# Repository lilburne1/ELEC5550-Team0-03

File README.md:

This project reflects the hardware and software contributions of Team 0-03 for ELEC5550 in pursuit of a free space optical laser communication system.

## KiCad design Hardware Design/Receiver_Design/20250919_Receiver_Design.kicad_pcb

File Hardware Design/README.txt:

This folder includes the hardware design for ELEC5550 Team0-03's FSO communication system.
This includes:
    The KiCad schematic and PCB manufacturing files for the laser receiver circuit
    The KiCad schematic and PCB manufacturing files for the laser driver circuit
    The KiCad schematic and PCB manufacturing files for the mainboards
    The 3D printing and CAD files for the system's enclosure and laser lens holder

All these materials are covered under the CERN-OHL-P license, as attached

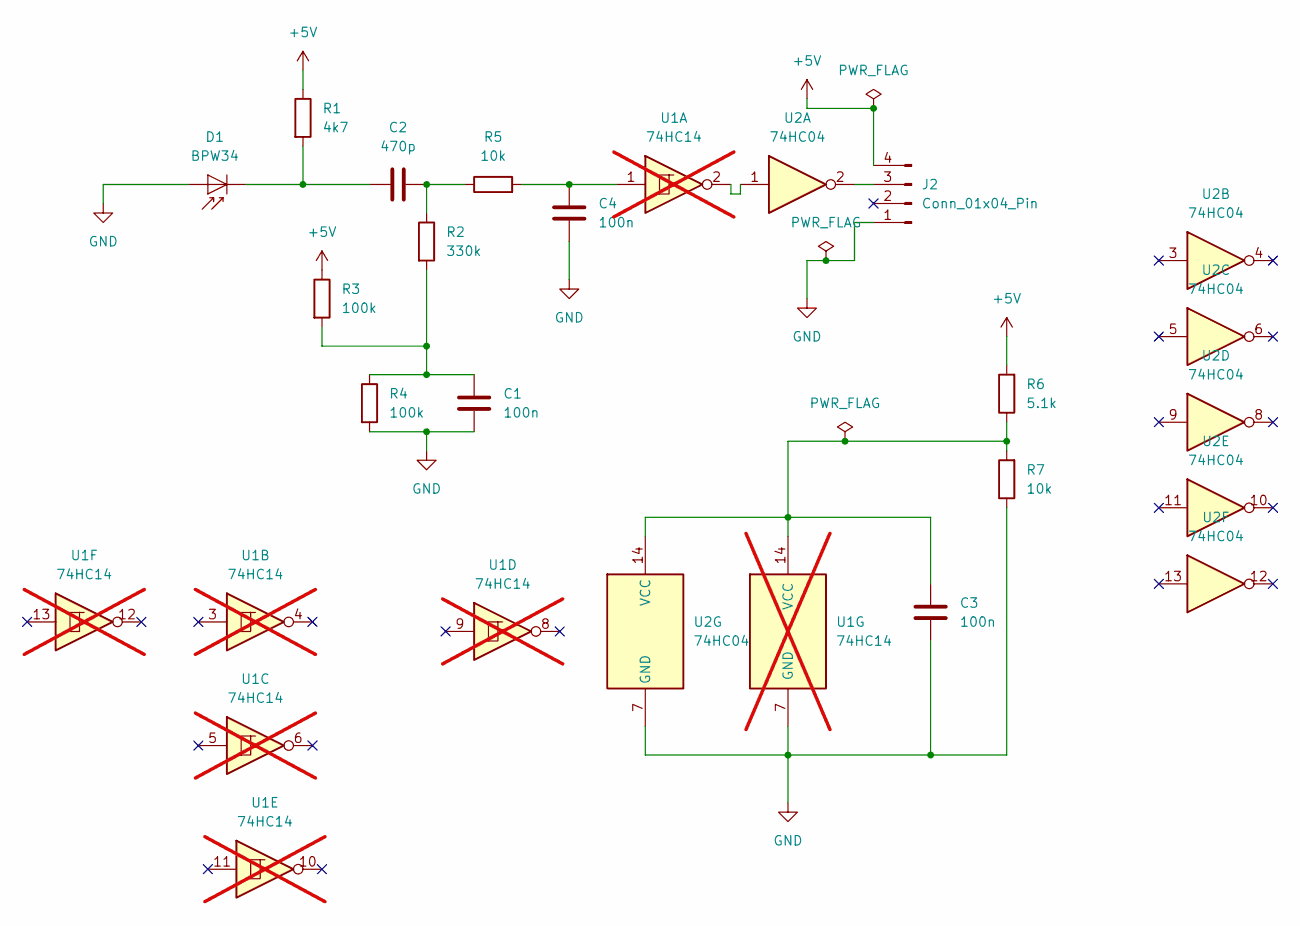
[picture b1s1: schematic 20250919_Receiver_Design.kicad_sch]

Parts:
C1, C3, C4: 100n; C_Disc_D4.7mm_W2.5mm_P5.00mm; JLC Component Number C14663
C2: 470p; C_Disc_D4.7mm_W2.5mm_P5.00mm; JLC Component Number C1588
D1: BPW34; Osram_DIL2_4.3x4.65mm_P5.08mm; JLC Component Number C85128
J2: Conn_01x04_Pin; PinHeader_1x04_P2.54mm_Vertical
R1: 4k7; R_Axial_DIN0207_L6.3mm_D2.5mm_P7.62mm_Horizontal; JLC Component Number C23162
R2: 330k; R_Axial_DIN0207_L6.3mm_D2.5mm_P7.62mm_Horizontal; JLC Component Number C22935
R3, R4: 100k; R_Axial_DIN0207_L6.3mm_D2.5mm_P7.62mm_Horizontal; JLC Component Number C23178
R5: 10k; R_Axial_DIN0207_L6.3mm_D2.5mm_P7.62mm_Horizontal; JLC Component Number C23162
R6: 5.1k; R_Axial_DIN0207_L6.3mm_D2.5mm_P7.62mm_Horizontal; JLC Component Number C22935
R7: 10k; R_Axial_DIN0207_L6.3mm_D2.5mm_P7.62mm_Horizontal; JLC Component Number C22935
U1: 74HC14; DIP-14_W7.62mm; not fitted
U2: 74HC04; DIP-14_W7.62mm

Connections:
+5V: J2.4, R1.1, R3.1, R6.2
GND: C1.2, C3.1, C4.1, D1.2 (A), J2.1, R4.2, R7.1, U1.7 (GND), U2.7 (GND)
unnamed: C1.1, R2.2, R3.2, R4.1
unnamed: C2.2, R2.1, R5.1
unnamed: C4.2, R5.2, U1.1
unnamed: C2.1, D1.1 (K), R1.2
unnamed: J2.3, U2.2
unnamed: U1.2, U2.1
unnamed: C3.2, R6.1, R7.2, U1.14 (VCC), U2.14 (VCC)

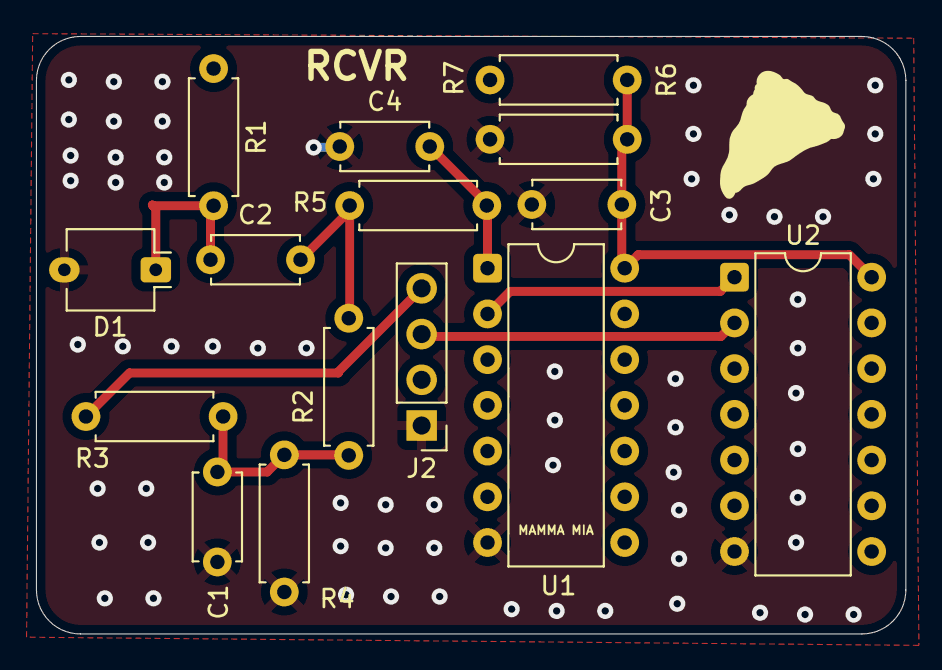
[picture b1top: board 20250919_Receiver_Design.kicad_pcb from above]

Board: 2 copper layers, 48.3 x 33.2 mm, 15 parts (0 on the bottom side), 9 nets.

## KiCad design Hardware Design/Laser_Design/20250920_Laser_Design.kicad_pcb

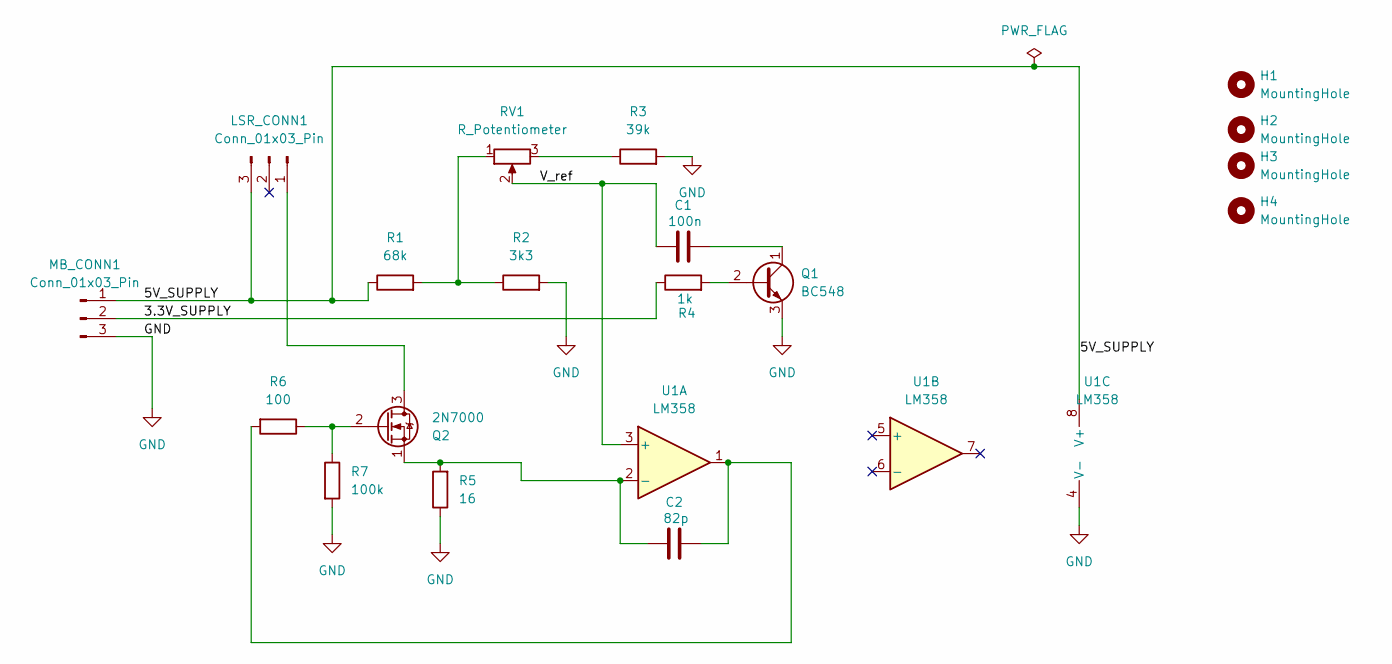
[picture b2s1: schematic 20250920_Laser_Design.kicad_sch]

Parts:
C1: 100n; C_Disc_D4.7mm_W2.5mm_P5.00mm
C2: 82p; C_Disc_D4.7mm_W2.5mm_P5.00mm
H1, H2, H3, H4: MountingHole; MountingHole_2.2mm_M2
LSR_CONN1: Conn_01x03_Pin; PinHeader_1x03_P2.54mm_Vertical
MB_CONN1: Conn_01x03_Pin; PinHeader_1x03_P2.54mm_Vertical
Q1: BC548; TO-92_Inline
Q2: 2N7000; TO-92_Inline
R1: 68k; R_Axial_DIN0207_L6.3mm_D2.5mm_P7.62mm_Horizontal
R2: 3k3; R_Axial_DIN0207_L6.3mm_D2.5mm_P7.62mm_Horizontal
R3: 39k; R_Axial_DIN0207_L6.3mm_D2.5mm_P7.62mm_Horizontal
R4: 1k; R_Axial_DIN0207_L6.3mm_D2.5mm_P7.62mm_Horizontal
R5: 16; R_Axial_DIN0207_L6.3mm_D2.5mm_P7.62mm_Horizontal
R6: 100; R_Axial_DIN0207_L6.3mm_D2.5mm_P7.62mm_Horizontal
R7: 100k; R_Axial_DIN0207_L6.3mm_D2.5mm_P7.62mm_Horizontal
RV1: R_Potentiometer; Potentiometer_Bourns_3296W_Vertical
U1: LM358; DIP-8_W7.62mm

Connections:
/3.3V_SUPPLY: MB_CONN1.2, R4.1
/5V_SUPPLY: LSR_CONN1.3, MB_CONN1.1, R1.1, U1.8 (V+); also elsewhere on the board
/V_ref: C1.1, RV1.2, U1.3 (+)
GND: MB_CONN1.3, Q1.3 (E), R2.2, R3.2, R5.1, R7.2, U1.4 (V-)
unnamed: C2.2, R6.2, U1.1
unnamed 5: LSR_CONN1.1, Q2.3 (D); also elsewhere on the board
unnamed: Q1.2 (B), R4.2
unnamed: C1.2, Q1.1 (C)
unnamed: Q2.2 (G), R6.1, R7.1
unnamed: C2.1, Q2.1 (S), R5.2, U1.2 (-)
unnamed: R1.2, R2.1, RV1.1
unnamed: R3.1, RV1.3

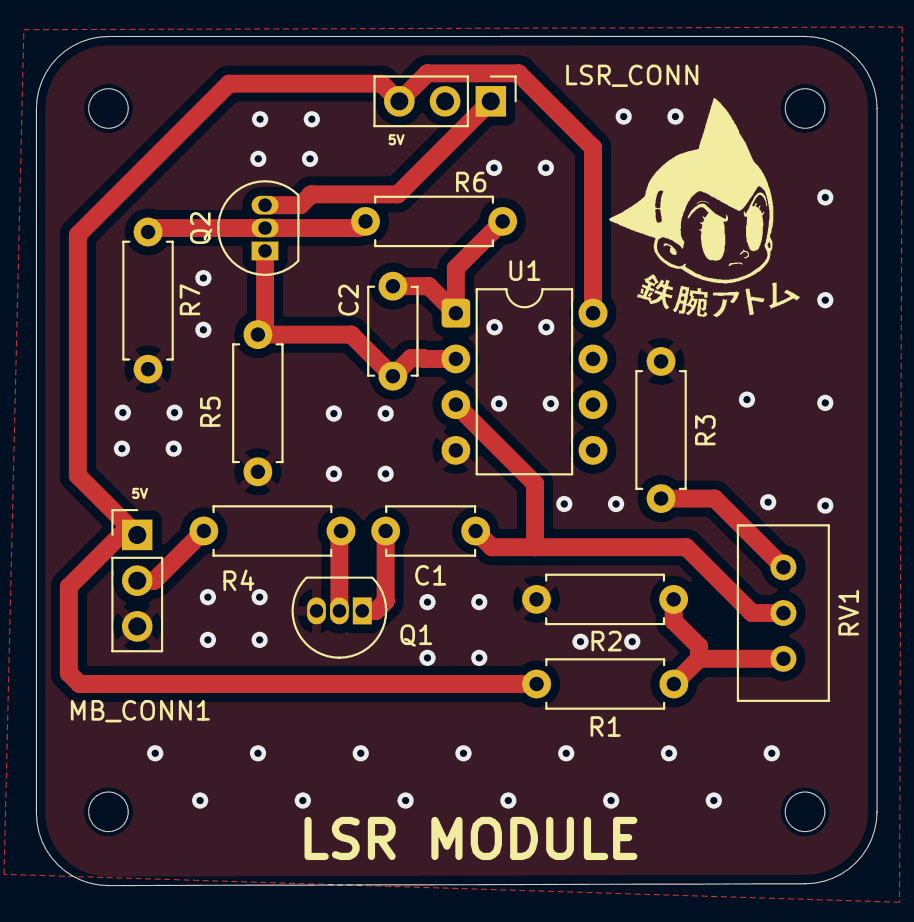
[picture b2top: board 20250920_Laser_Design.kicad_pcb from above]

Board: 2 copper layers, 46.7 x 47.2 mm, 19 parts (0 on the bottom side), 12 nets.

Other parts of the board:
LSR_CONN: Conn_01x03_Pin; PinHeader_1x03_P2.54mm_Vertical

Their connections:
/5V_SUPPLY: LSR_CONN.3; also elsewhere on the board
unnamed 5: LSR_CONN.1; also elsewhere on the board

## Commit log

2025-08-26 Created Repository Structure
2025-08-26 Cleanup
2025-10-26 File Clean Up
